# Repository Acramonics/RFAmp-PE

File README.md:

High-gain RF Preamp
===================

**Circuit (c) 2026, Mike Tooley, Practical Electronics**

**PCB (c) 2026, Andrew Martin, acramonics**

This circuit was published in *Practical Electronics*, September 2026 as part of the *Teach-In 2026* series, *World of Wireless - An Introduction to Radio and Wireless Technology*

For details, see that issue.

Components
----------

Capacitors, FETs and connectors are all from AliExpress.

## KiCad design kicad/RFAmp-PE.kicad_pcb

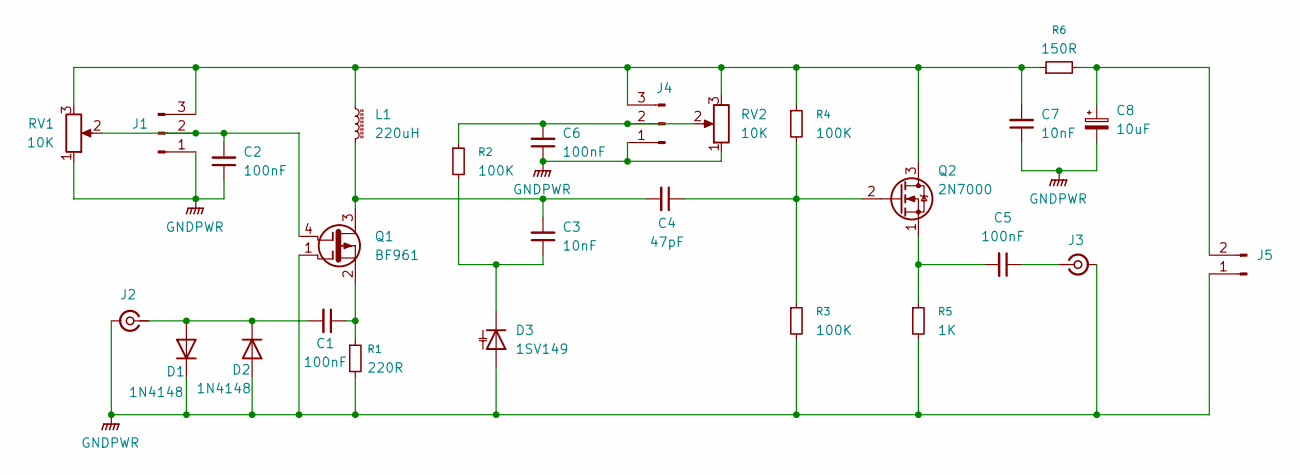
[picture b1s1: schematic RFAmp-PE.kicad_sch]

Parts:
C1, C2, C5, C6: 100nF; C_Disc_D4.7mm_W2.5mm_P5.00mm
C3, C7: 10nF; C_Disc_D4.7mm_W2.5mm_P5.00mm
C4: 47pF; C_Disc_D4.7mm_W2.5mm_P5.00mm
C8: 10uF; CP_Radial_D5.0mm_P2.50mm
D1, D2: 1N4148; D_DO-35_SOD27_P7.62mm_Horizontal
D3: 1SV149; TO-92-2S
J1, J4: Conn_01x03_Pin; Molex_KK-254_AE-6410-03A_1x03_P2.54mm_Vertical
J2, J3: Conn_Coaxial_Small; SMA_Vertical_AliExpress
J5: Conn_01x02_Pin; Molex_KK-254_AE-6410-02A_1x02_P2.54mm_Vertical
L1: 220uH; L_Axial_L7.0mm_D3.3mm_P10.16mm_Horizontal_Fastron_MICC
Q1: BF961; BF961_TO50
Q2: 2N7000; TO-92_Inline
R1: 220R; R_Axial_DIN0207_L6.3mm_D2.5mm_P10.16mm_Horizontal
R2, R3, R4: 100K; R_Axial_DIN0207_L6.3mm_D2.5mm_P10.16mm_Horizontal
R5: 1K; R_Axial_DIN0207_L6.3mm_D2.5mm_P10.16mm_Horizontal
R6: 150R; R_Axial_DIN0207_L6.3mm_D2.5mm_P10.16mm_Horizontal
RV1, RV2: 10K; R_Axial_DIN0207_L6.3mm_D2.5mm_P10.16mm_Horizontal

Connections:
GNDPWR: C2.1, C6.1, C7.1, C8.2, D1.1 (K), D2.2 (A), D3.2 (A), J1.1, J2.2 (Ext), J3.2 (Ext), J4.1, J5.1, Q1.1 (G1), R1.2, R3.2, R5.2, RV1.1, RV2.1
unnamed: C1.2, D1.2 (A), D2.1 (K), J2.1 (In)
unnamed: C3.1, D3.1 (K), R2.2
unnamed: C2.2, J1.2, Q1.4 (G2), RV1.2
unnamed: C7.2, J1.3, J4.3, L1.1, Q2.3 (D), R4.1, R6.1, RV1.3, RV2.3
unnamed: C5.1, J3.1 (In)
unnamed: C6.2, J4.2, R2.1, RV2.2
unnamed: C8.1, J5.2, R6.2
unnamed: C3.2, C4.2, L1.2, Q1.3 (D)
unnamed: C1.1, Q1.2 (S), R1.1
unnamed: C4.1, Q2.2 (G), R3.1, R4.2
unnamed: C5.2, Q2.1 (S), R5.1

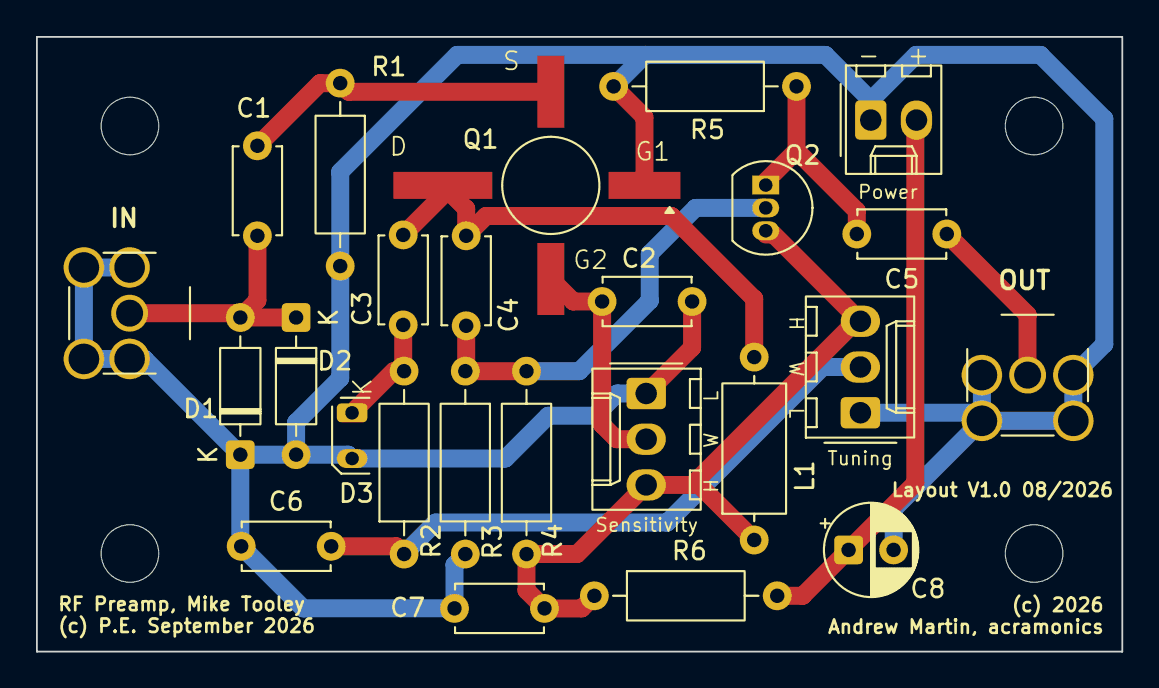
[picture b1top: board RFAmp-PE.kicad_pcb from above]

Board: 2 copper layers, 60.3 x 34.2 mm, 25 parts (0 on the bottom side), 12 nets.
